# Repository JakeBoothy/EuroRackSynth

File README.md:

# Eurorack Synth
A eurorack synthesizer.

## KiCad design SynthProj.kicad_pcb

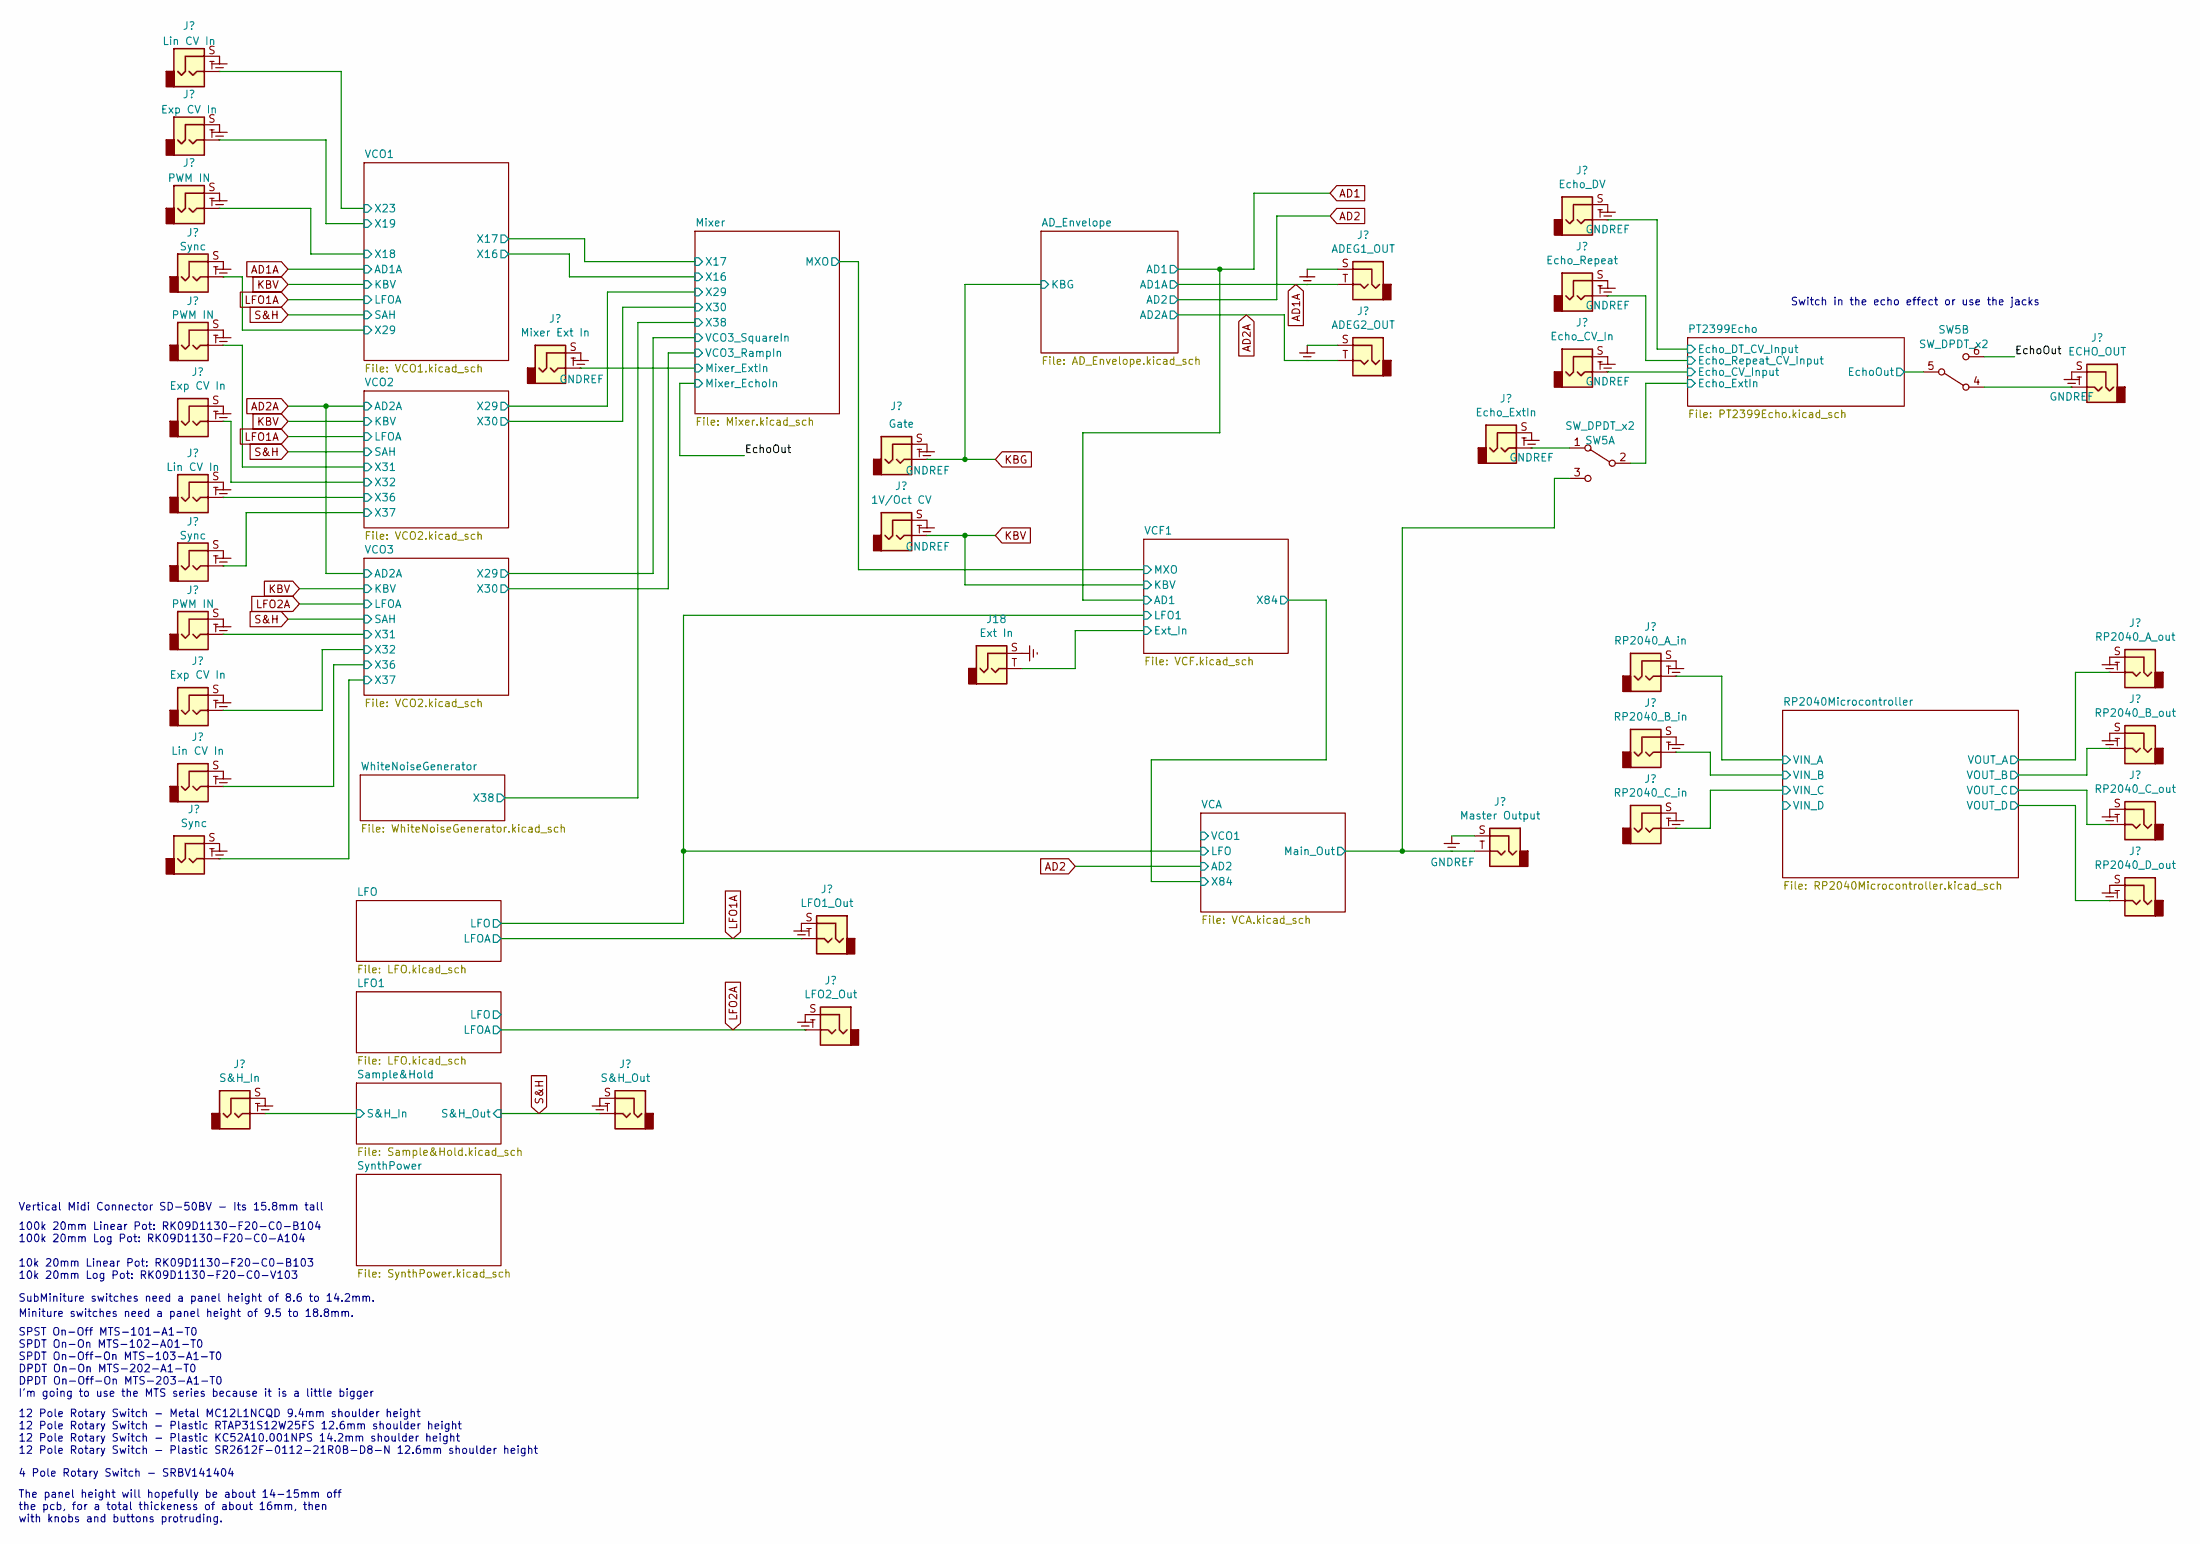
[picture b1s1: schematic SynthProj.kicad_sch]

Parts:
J1, J9, J17: PWM IN; PJ-301-BM
J2, J8, J19: Exp CV In; PJ-301-BM
J3, J7, J22: Lin CV In; PJ-301-BM
J4, J23, J24: Sync; PJ-301-BM
J6: S&H_In; PJ-301-BM
J10: Mixer Ext In; PJ-301-BM
J11: S&H_Out; PJ-301-BM
J12: LFO1_Out; PJ-301-BM
J13: Gate; PJ-301-BM
J14: 1V/Oct CV; PJ-301-BM
J16: LFO2_Out; PJ-301-BM
J18: Ext In; PJ-301-BM
J20: ADEG1_OUT; PJ-301-BM
J21: ADEG2_OUT; PJ-301-BM
J25: Master Output; PJ-301-BM
J26: RP2040_A_in; PJ-301-BM
J27: RP2040_B_in; PJ-301-BM
J28: RP2040_C_in; PJ-301-BM
J30: Echo_DV; PJ-301-BM
J31: Echo_Repeat; PJ-301-BM
J32: Echo_CV_In; PJ-301-BM
J33: Echo_ExtIn; PJ-301-BM
J34: ECHO_OUT; PJ-301-BM
J35: RP2040_A_out; PJ-301-BM
J36: RP2040_B_out; PJ-301-BM
J37: RP2040_C_out; PJ-301-BM
J38: RP2040_D_out; PJ-301-BM
SW5: SW_DPDT_x2; SMTS-202

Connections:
/EchoOut: SW5.6 (C); also elsewhere on the board
/Mixer/Mixer_ExtIn: J10.T; also elsewhere on the board
/PT2399Echo/EchoOut: SW5.5 (B); also elsewhere on the board
/PT2399Echo/Echo_CV_Input: J32.T; also elsewhere on the board
/PT2399Echo/Echo_DT_CV_Input: J30.T; also elsewhere on the board
/PT2399Echo/Echo_ExtIn: SW5.2 (B); also elsewhere on the board
/PT2399Echo/Echo_Repeat_CV_Input: J31.T; also elsewhere on the board
/RP2040Microcontroller/VIN_A: J26.T; also elsewhere on the board
/RP2040Microcontroller/VIN_B: J27.T; also elsewhere on the board
/RP2040Microcontroller/VIN_C: J28.T; also elsewhere on the board
/RP2040Microcontroller/VOUT_A: J35.T; also elsewhere on the board
/RP2040Microcontroller/VOUT_B: J36.T; also elsewhere on the board
/RP2040Microcontroller/VOUT_C: J37.T; also elsewhere on the board
/RP2040Microcontroller/VOUT_D: J38.T; also elsewhere on the board
/Sample&Hold/S&H_In: J6.T; also elsewhere on the board
/VCA/Main_Out: J25.T, SW5.3 (C); also elsewhere on the board
/VCO1/X18: J9.T; also elsewhere on the board
/VCO1/X19: J8.T; also elsewhere on the board
/VCO1/X23: J7.T; also elsewhere on the board
/VCO1/X29: J24.T; also elsewhere on the board
/VCO2/X31: J1.T; also elsewhere on the board
/VCO2/X32: J2.T; also elsewhere on the board
/VCO2/X36: J3.T; also elsewhere on the board
/VCO2/X37: J23.T; also elsewhere on the board
/VCO3/X31: J17.T; also elsewhere on the board
/VCO3/X32: J19.T; also elsewhere on the board
/VCO3/X36: J22.T; also elsewhere on the board
/VCO3/X37: J4.T; also elsewhere on the board
AD1A: J20.T; also elsewhere on the board
AD2A: J21.T; also elsewhere on the board
GNDREF: J1.S, J2.S, J3.S, J4.S, J6.S, J7.S, J8.S, J9.S, J10.S, J11.S, J12.S, J13.S, J14.S, J16.S, J17.S, J18.S, J19.S, J20.S, J21.S, J22.S, J23.S, J24.S, J25.S, J26.S, J27.S, J28.S, J30.S, J31.S, J32.S, J33.S, J34.S, J35.S, J36.S, J37.S, J38.S; also elsewhere on the board
KBG: J13.T; also elsewhere on the board
KBV: J14.T; also elsewhere on the board
LFO1A: J12.T; also elsewhere on the board
LFO2A: J16.T; also elsewhere on the board
unnamed: J33.T, SW5.1 (A)
unnamed: J34.T, SW5.4 (A)
S&H: J11.T; also elsewhere on the board
X7: J18.T; also elsewhere on the board

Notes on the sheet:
SubMiniture switches need a panel height of 8.6 to 14.2mm.
Vertical Midi Connector SD-50BV - Its 15.8mm tall
Switch in the echo effect or use the jacks
100k 20mm Linear Pot: RK09D1130-F20-C0-B104 100k 20mm Log Pot: RK09D1130-F20-C0-A104 10k 20mm Linear Pot: RK09D1130-F20-C0-B103 10k 20mm Log Pot: RK09D1130-F20-C0-V103
4 Pole Rotary Switch - SRBV141404
The panel height will hopefully be about 14-15mm off the pcb, for a total thickeness of about 16mm, then with knobs and buttons protruding.
SPST On-Off MTS-101-A1-T0 SPDT On-On MTS-102-A01-T0 SPDT On-Off-On MTS-103-A1-T0 DPDT On-On MTS-202-A1-T0 DPDT On-Off-On MTS-203-A1-T0 I'm going to use the MTS series because it is a little bigger
Miniture switches need a panel height of 9.5 to 18.8mm.
12 Pole Rotary Switch - Metal MC12L1NCQD 9.4mm shoulder height 12 Pole Rotary Switch - Plastic RTAP31S12W25FS 12.6mm shoulder height 12 Pole Rotary Switch - Plastic KC52A10.001NPS 14.2mm shoulder height 12 Pole Rotary Switch - Plastic SR2612F-0112-21R0B-D8-N 12.6mm shoulder height

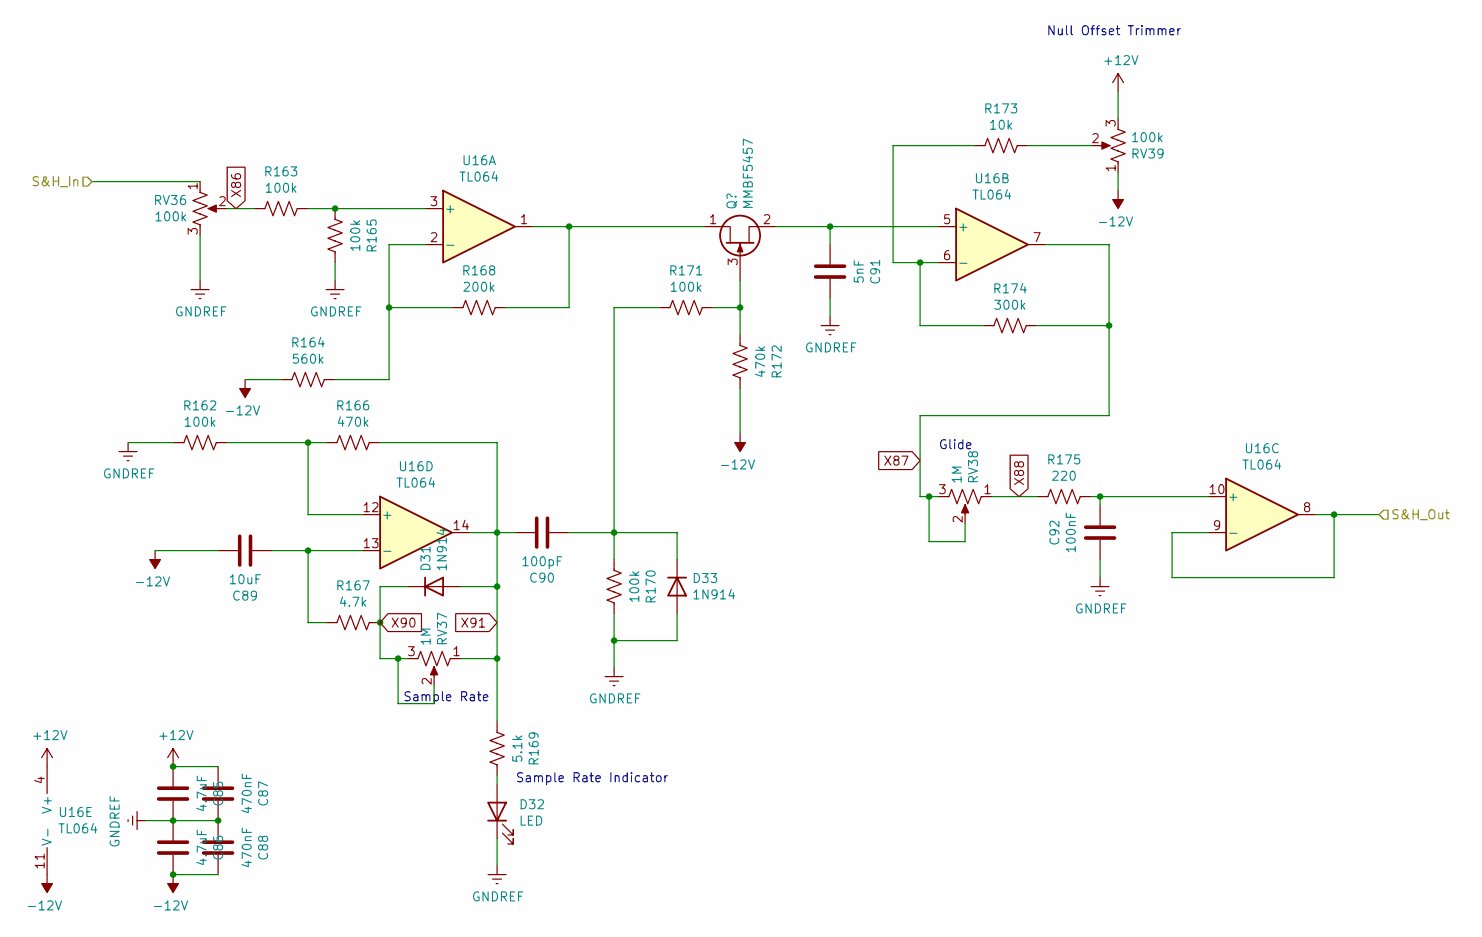
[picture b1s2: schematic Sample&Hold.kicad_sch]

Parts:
C85, C86: 4.7uF; C_0805_2012Metric
C87, C88: 470nF; C_0805_2012Metric
C89: 10uF; C_0805_2012Metric
C90: 100pF; C_0603_1608Metric
C91: 5nF; C_0603_1608Metric
C92: 100nF; C_0603_1608Metric
D31, D33: 1N914; D_SOD-323F
D32: LED; LED_0805_2012Metric
Q19: MMBF5457; SOT-23-3
R162, R163, R165, R170, R171: 100k; R_0603_1608Metric
R164: 560k; R_0603_1608Metric
R166, R172: 470k; R_0603_1608Metric
R167: 4.7k; R_0603_1608Metric
R168: 200k; R_0603_1608Metric
R169: 5.1k; R_0603_1608Metric
R173: 10k; R_0603_1608Metric
R174: 300k; R_0603_1608Metric
R175: 220; R_0603_1608Metric
RV36: 100k; Potentiometer_Alps_RK09K_Single_Vertical
RV37, RV38: 1M; Potentiometer_Alps_RK09K_Single_Vertical
RV39: 100k; Potentiometer_Bourns_TC33X_Vertical
U16: TL064; SO-14_3.9x8.65mm_P1.27mm

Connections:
+12V: C85.2, C87.2, RV39.3, U16.4 (V+); also elsewhere on the board
-12V: C86.1, C88.1, C89.1, R164.2, R172.1, RV39.1, U16.11 (V-); also elsewhere on the board
/Sample&Hold/S&H_In: RV36.1; also elsewhere on the board
GNDREF: C85.1, C86.2, C87.1, C88.2, C91.1, C92.2, D32.1 (K), D33.2 (A), R162.2, R165.1, R170.1, RV36.3; also elsewhere on the board
unnamed: D32.2 (A), R169.1
unnamed: C90.2, D33.1 (K), R170.2, R171.2
unnamed: Q19.1 (D), R168.1, U16.1
unnamed: Q19.3 (G), R171.1, R172.2
unnamed: C91.2, Q19.2 (S), U16.5 (+)
unnamed: R173.1, RV39.2
unnamed: R163.1, R165.2, U16.3 (+)
unnamed: R164.1, R168.2, U16.2 (-)
unnamed: R173.2, R174.2, U16.6 (-)
unnamed: C92.1, R175.1, U16.10 (+)
unnamed: R162.1, R166.2, U16.12 (+)
unnamed: C89.2, R167.2, U16.13 (-)
S&H: U16.8, U16.9 (-); also elsewhere on the board
X86: R163.2, RV36.2
X87: R174.1, RV38.2, RV38.3, U16.7
X88: R175.2, RV38.1
X90: D31.1 (K), R167.1, RV37.2, RV37.3
X91: C90.1, D31.2 (A), R166.1, R169.2, RV37.1, U16.14

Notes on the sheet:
Sample Rate Indicator
Sample Rate
Glide
Null Offset Trimmer

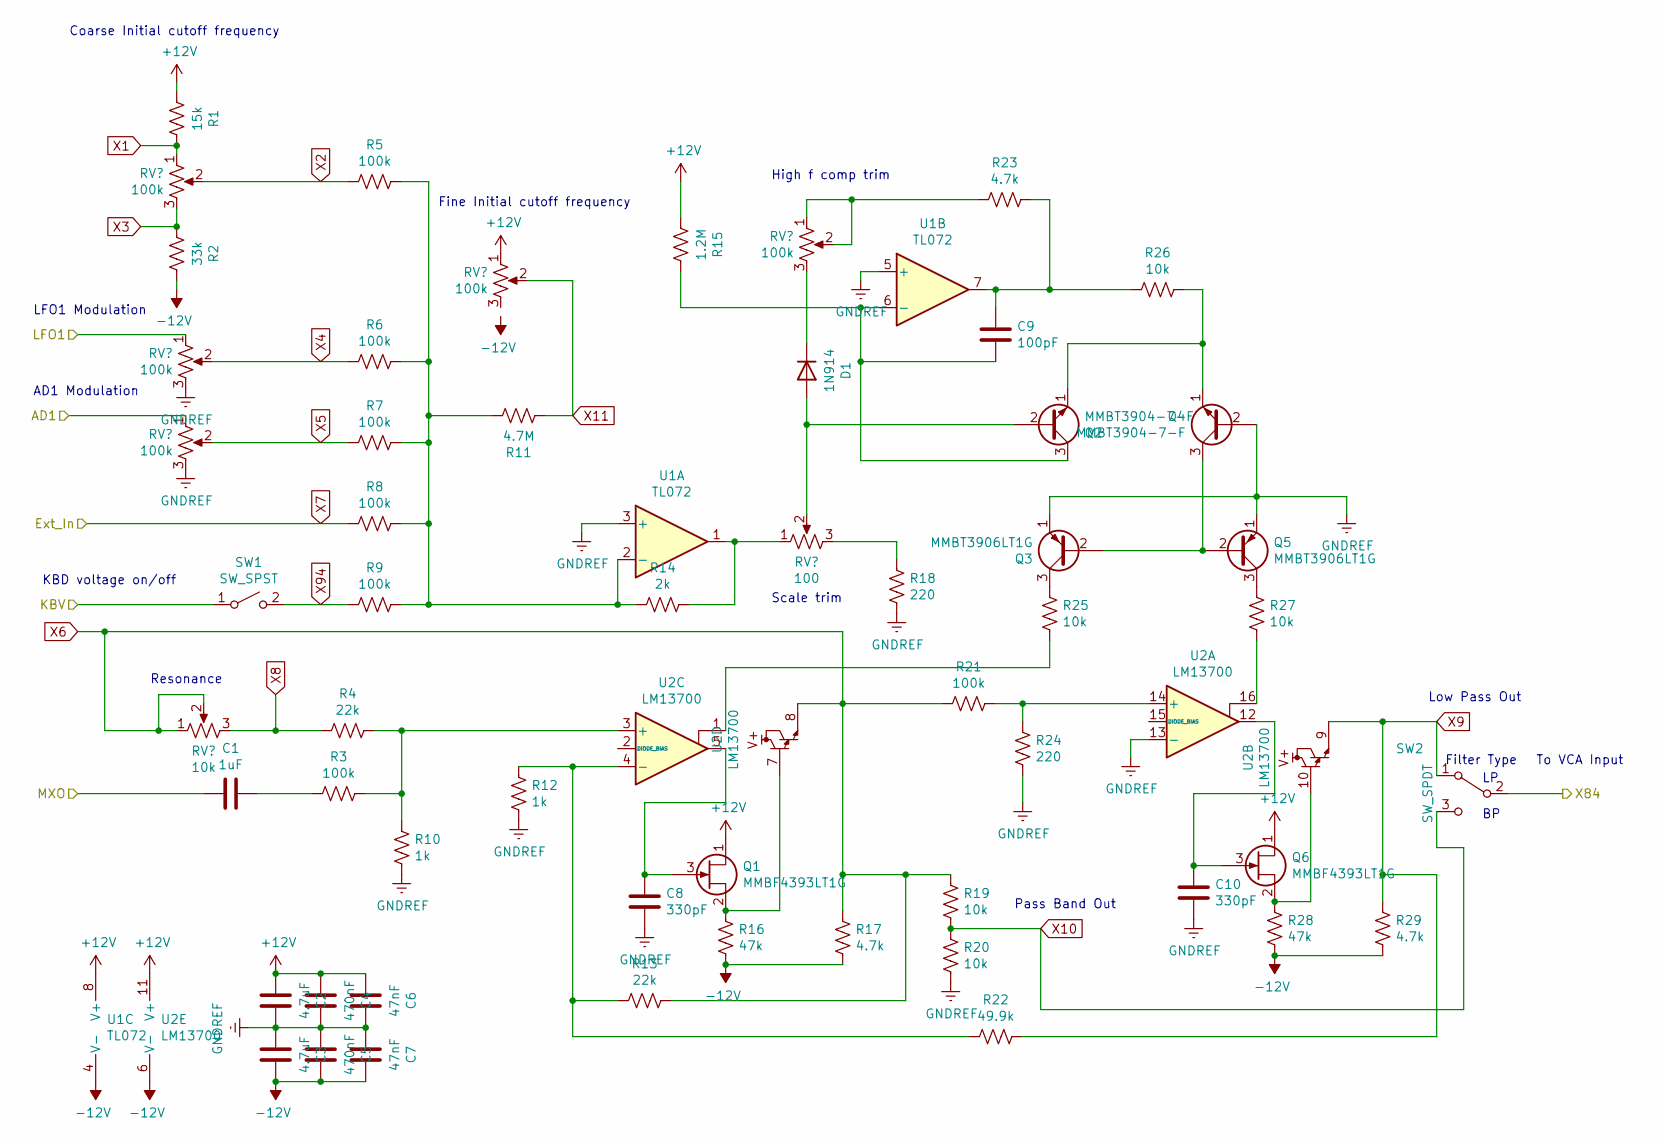
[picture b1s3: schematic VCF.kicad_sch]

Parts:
C1: 1uF; C_0805_2012Metric
C2, C3: 4.7uF; C_0805_2012Metric
C4, C5: 470nF; C_0805_2012Metric
C6, C7: 47nF; C_0603_1608Metric
C8, C10: 330pF; C_0603_1608Metric
C9: 100pF; C_0603_1608Metric
D1: 1N914; D_SOD-323F
Q1, Q6: MMBF4393LT1G; SOT-23-3
Q2, Q4: MMBT3904-7-F; SOT-23-3
Q3, Q5: MMBT3906LT1G; SOT-23-3
R1: 15k; R_0603_1608Metric
R2: 33k; R_0603_1608Metric
R3, R5, R6, R7, R8, R9, R21: 100k; R_0603_1608Metric
R4, R13: 22k; R_0603_1608Metric
R10, R12: 1k; R_0603_1608Metric
R11: 4.7M; R_0603_1608Metric
R14: 2k; R_0603_1608Metric
R15: 1.2M; R_0603_1608Metric
R16, R28: 47k; R_0603_1608Metric
R17, R23, R29: 4.7k; R_0603_1608Metric
R18, R24: 220; R_0603_1608Metric
R19, R20, R25, R26, R27: 10k; R_0603_1608Metric
R22: 49.9k; R_0603_1608Metric
RV1, RV2, RV3, RV5: 100k; Potentiometer_Alps_RK09K_Single_Vertical
RV4: 10k; Potentiometer_Alps_RK09K_Single_Vertical
RV6: 100k; Potentiometer_Bourns_TC33X_Vertical
RV7: 100; Potentiometer_Bourns_TC33X_Vertical
SW1: SW_SPST; SMTS-102
SW2: SW_SPDT; SMTS-102
U1: TL072; SOP-8_3.9x4.9mm_P1.27mm
U2: LM13700; SO-16_5.3x10.2mm_P1.27mm

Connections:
+12V: C2.2, C4.2, C6.2, Q1.1 (D), Q6.1 (D), R1.2, R15.2, RV5.1, U1.8 (V+), U2.11 (V+); also elsewhere on the board
-12V: C3.1, C5.1, C7.1, R2.1, R16.1, R17.1, R28.1, R29.1, U1.4 (V-), U2.6 (V-); also elsewhere on the board
/LFO/LFO: RV2.1; also elsewhere on the board
/Mixer/MXO: C1.2; also elsewhere on the board
/VCA/X84: SW2.2 (B); also elsewhere on the board
AD1: RV3.1; also elsewhere on the board
GNDREF: C2.1, C3.2, C4.1, C5.2, C6.1, C7.2, C8.2, C10.2, Q3.1 (E), Q4.2 (B), Q5.1 (E), R10.2, R12.2, R18.2, R20.2, R24.1, RV2.3, RV3.3, U1.3 (+), U1.5 (+), U2.13 (-); also elsewhere on the board
KBV: SW1.1 (A); also elsewhere on the board
unnamed: C1.1, R3.2
unnamed: C9.1, R23.1, R26.2, U1.7
unnamed: D1.2 (A), Q2.2 (B), RV7.2
unnamed: D1.1 (K), RV6.3
unnamed: C8.1, Q1.3 (G), U2.5
unnamed: Q1.2 (S), R16.2, U2.7
unnamed: C9.2, Q2.3 (C), R15.1, U1.6 (-)
unnamed: Q2.1 (E), Q4.1 (E), R26.1
unnamed: Q3.2 (B), Q4.3 (C), Q5.2 (B)
unnamed: Q3.3 (C), R25.1
unnamed: Q5.3 (C), R27.1
unnamed: C10.1, Q6.3 (G), U2.12
unnamed: Q6.2 (S), R28.2, U2.10
unnamed: R14.1, RV7.1, U1.1
unnamed: R18.1, RV7.3
unnamed: R23.2, RV6.1, RV6.2
unnamed: R25.2, U2.1
unnamed: R27.2, U2.16
unnamed: R5.1, R6.1, R7.1, R8.1, R9.1, R11.1, R14.2, U1.2 (-)
unnamed: R21.1, R24.2, U2.14 (+)
unnamed: R3.1, R4.1, R10.1, U2.3 (+)
unnamed: R12.1, R13.1, R22.1, U2.4 (-)
X1: R1.1, RV1.1
X2: R5.2, RV1.2
X3: R2.2, RV1.3
X4: R6.2, RV2.2
X5: R7.2, RV3.2
X6: R13.2, R17.2, R19.1, R21.2, RV4.1, RV4.2, U2.8
X7: R8.2; also elsewhere on the board
X8: R4.2, RV4.3
X9: R22.2, R29.2, SW2.1 (A), U2.9
X10: R19.2, R20.1, SW2.3 (C)
X11: R11.2, RV5.2
X94: R9.2, SW1.2 (B)

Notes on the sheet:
KBD voltage on/off
AD1 Modulation
Resonance
Low Pass Out
Fine Initial cutoff frequency
LFO1 Modulation
Coarse Initial cutoff frequency
Scale trim
To VCA Input
Filter Type
High f comp trim
Pass Band Out

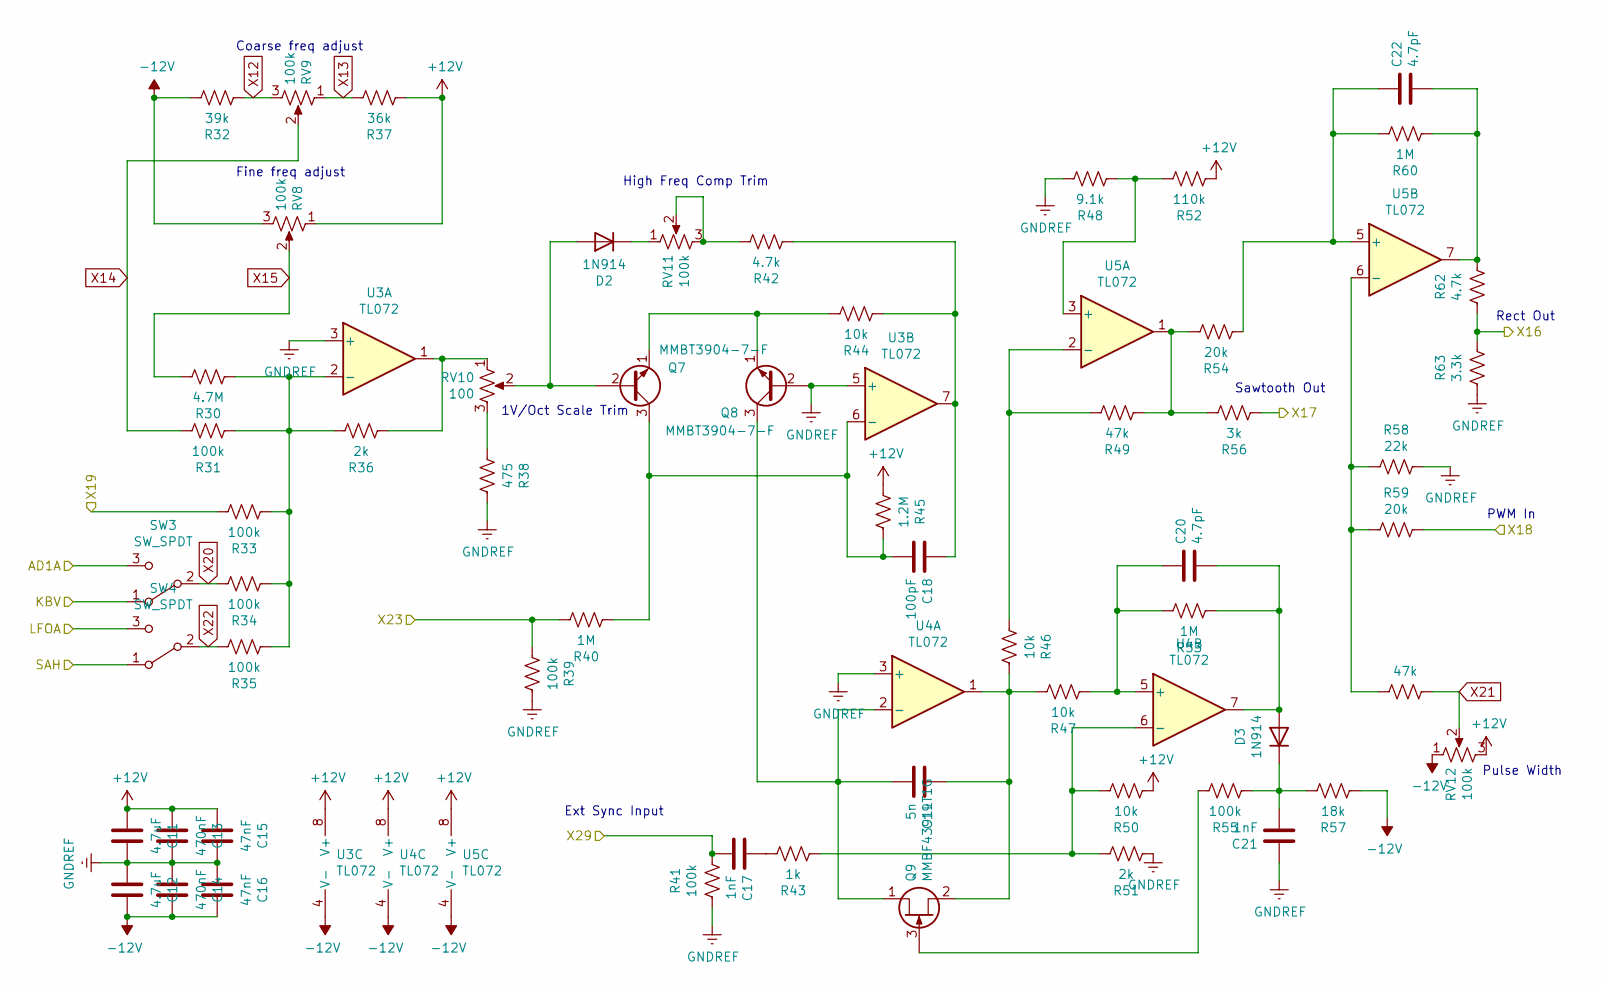
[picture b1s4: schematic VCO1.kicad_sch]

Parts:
C11, C12: 4.7uF; C_0805_2012Metric
C13, C14: 470nF; C_0805_2012Metric
C15, C16: 47nF; C_0603_1608Metric
C17, C21: 1nF; C_0603_1608Metric
C18: 100pF; C_0603_1608Metric
C19: 5n; C_0603_1608Metric
C20, C22: 4.7pF; C_0603_1608Metric
D2, D3: 1N914; D_SOD-323F
Q7, Q8: MMBT3904-7-F; SOT-23-3
Q9: MMBF4391LT1G; SOT-23-3
R30: 4.7M; R_0603_1608Metric
R31, R33, R34, R35, R39, R41, R55: 100k; R_0603_1608Metric
R32: 39k; R_0603_1608Metric
R36, R51: 2k; R_0603_1608Metric
R37: 36k; R_0603_1608Metric
R38: 475; R_0603_1608Metric
R40, R53, R60: 1M; R_0603_1608Metric
R42, R62: 4.7k; R_0603_1608Metric
R43: 1k; R_0603_1608Metric
R44, R46, R47, R50: 10k; R_0603_1608Metric
R45: 1.2M; R_0603_1608Metric
R48: 9.1k; R_0603_1608Metric
R49, R61: 47k; R_0603_1608Metric
R52: 110k; R_0603_1608Metric
R54, R59: 20k; R_0603_1608Metric
R56: 3k; R_0603_1608Metric
R57: 18k; R_0603_1608Metric
R58: 22k; R_0603_1608Metric
R63: 3.3k; R_0603_1608Metric
RV8, RV9, RV12: 100k; Potentiometer_Alps_RK09K_Single_Vertical
RV10: 100; Potentiometer_Bourns_TC33X_Vertical
RV11: 100k; Potentiometer_Bourns_TC33X_Vertical
SW3, SW4: SW_SPDT; SMTS-102
U3, U4, U5: TL072; SO-8_3.9x4.9mm_P1.27mm

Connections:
+12V: C11.2, C13.2, C15.2, R37.2, R45.2, R50.2, R52.2, RV8.1, RV12.3, U3.8 (V+), U4.8 (V+), U5.8 (V+); also elsewhere on the board
-12V: C12.1, C14.1, C16.1, R32.1, R57.2, RV8.3, RV12.1, U3.4 (V-), U4.4 (V-), U5.4 (V-); also elsewhere on the board
/Mixer/X16: R62.2, R63.1; also elsewhere on the board
/Mixer/X17: R56.2; also elsewhere on the board
/VCO1/X18: R59.1; also elsewhere on the board
/VCO1/X19: R33.1; also elsewhere on the board
/VCO1/X23: R39.2, R40.1; also elsewhere on the board
/VCO1/X29: C17.2, R41.1; also elsewhere on the board
AD1A: SW3.3 (C); also elsewhere on the board
GNDREF: C11.1, C12.2, C13.1, C14.2, C15.1, C16.2, C21.1, Q8.2 (B), R38.1, R39.1, R41.2, R48.1, R51.2, R58.1, R63.2, U3.3 (+), U3.5 (+), U4.3 (+); also elsewhere on the board
KBV: SW3.1 (A); also elsewhere on the board
LFO1A: SW4.3 (C); also elsewhere on the board
unnamed: C17.1, R43.1
unnamed: C18.1, R42.2, R44.2, U3.7
unnamed: C22.2, R60.2, R62.1, U5.7
unnamed: D2.2 (A), Q7.2 (B), RV10.2
unnamed: C20.2, D3.2 (A), R53.2, U4.7
unnamed: C21.2, D3.1 (K), R55.2, R57.1
unnamed: C18.2, Q7.3 (C), R40.2, R45.1, U3.6 (-)
unnamed: Q7.1 (E), Q8.1 (E), R44.1
unnamed: C19.2, Q8.3 (C), Q9.1 (D), U4.2 (-)
unnamed: Q9.3 (G), R55.1
unnamed: C19.1, Q9.2 (S), R46.1, R47.1, U4.1
unnamed: R36.2, RV10.1, U3.1
unnamed: R38.2, RV10.3
unnamed: R49.2, R54.1, R56.1, U5.1
unnamed: R30.2, R31.2, R33.2, R34.2, R35.2, R36.1, U3.2 (-)
unnamed: C20.1, R47.2, R53.1, U4.5 (+)
unnamed: R43.2, R50.1, R51.1, U4.6 (-)
unnamed: R48.2, R52.1, U5.3 (+)
unnamed: R46.2, R49.1, U5.2 (-)
unnamed: C22.1, R54.2, R60.1, U5.5 (+)
unnamed: R58.2, R59.2, R61.2, U5.6 (-)
S&H: SW4.1 (A); also elsewhere on the board
X12: R32.2, RV9.3
X13: R37.1, RV9.1
X14: R31.1, RV9.2
X15: R30.1, RV8.2
X20: R34.1, SW3.2 (B)
X21: R61.1, RV12.2
X22: R35.1, SW4.2 (B)

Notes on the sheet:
Pulse Width
Coarse freq adjust
High Freq Comp Trim
Fine freq adjust
Rect Out
1V/Oct Scale Trim
Ext Sync Input
PWM In
Sawtooth Out

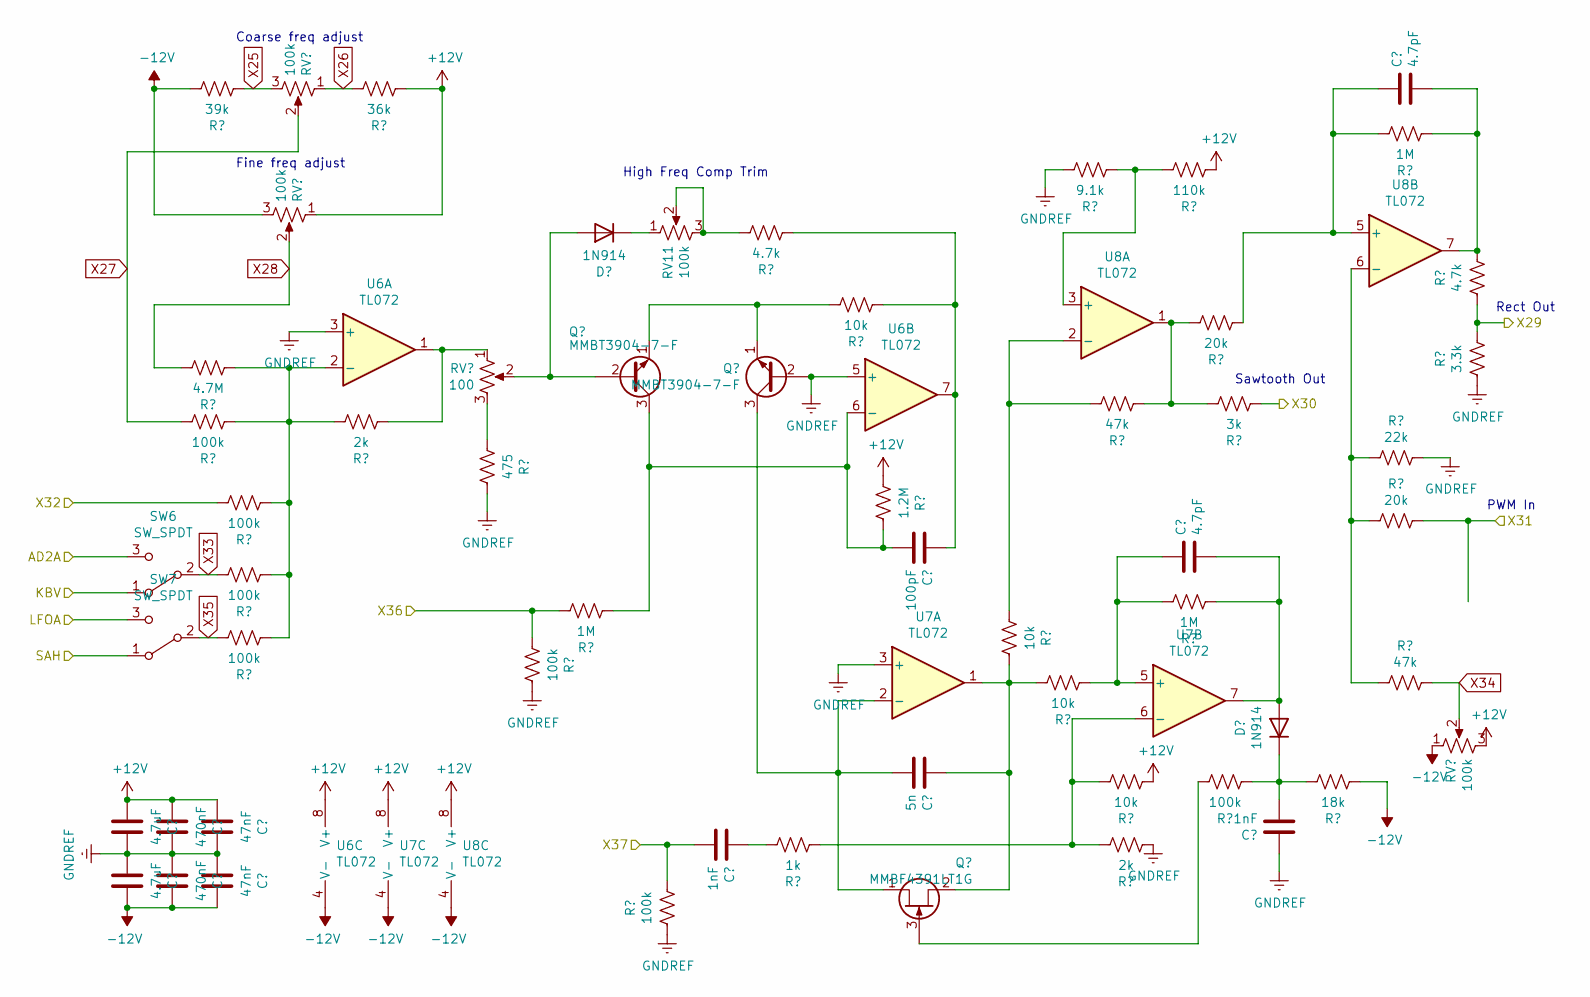
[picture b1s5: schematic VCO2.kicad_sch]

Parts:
C23, C24: 4.7uF; C_0805_2012Metric
C25, C26: 470nF; C_0805_2012Metric
C27, C28: 47nF; C_0603_1608Metric
C29, C33: 1nF; C_0603_1608Metric
C30: 100pF; C_0603_1608Metric
C31: 5n; C_0603_1608Metric
C32, C34: 4.7pF; C_0603_1608Metric
D4, D5: 1N914; D_SOD-323F
Q10, Q11: MMBT3904-7-F; SOT-23-3
Q12: MMBF4391LT1G; SOT-23-3
R64: 4.7M; R_0603_1608Metric
R65, R67, R68, R69, R73, R75, R89: 100k; R_0603_1608Metric
R66: 39k; R_0603_1608Metric
R70, R85: 2k; R_0603_1608Metric
R71: 36k; R_0603_1608Metric
R72: 475; R_0603_1608Metric
R74, R87, R94: 1M; R_0603_1608Metric
R76, R96: 4.7k; R_0603_1608Metric
R77: 1k; R_0603_1608Metric
R78, R80, R81, R84: 10k; R_0603_1608Metric
R79: 1.2M; R_0603_1608Metric
R82: 9.1k; R_0603_1608Metric
R83, R95: 47k; R_0603_1608Metric
R86: 110k; R_0603_1608Metric
R88, R93: 20k; R_0603_1608Metric
R90: 3k; R_0603_1608Metric
R91: 18k; R_0603_1608Metric
R92: 22k; R_0603_1608Metric
R97: 3.3k; R_0603_1608Metric
RV11: 100k; Potentiometer_Bourns_TC33X_Vertical
RV13, RV14, RV17: 100k; Potentiometer_Alps_RK09K_Single_Vertical
RV15: 100; Potentiometer_Bourns_TC33X_Vertical
SW6, SW7: SW_SPDT; SMTS-102
U6, U7, U8: TL072; SO-8_3.9x4.9mm_P1.27mm

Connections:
+12V: C23.2, C25.2, C27.2, R71.2, R79.2, R84.2, R86.2, RV13.1, RV17.3, U6.8 (V+), U7.8 (V+), U8.8 (V+); also elsewhere on the board
-12V: C24.1, C26.1, C28.1, R66.1, R91.2, RV13.3, RV17.1, U6.4 (V-), U7.4 (V-), U8.4 (V-); also elsewhere on the board
/Mixer/X29: R96.2, R97.1; also elsewhere on the board
/Mixer/X30: R90.2; also elsewhere on the board
/VCO2/X31: R93.1; also elsewhere on the board
/VCO2/X32: R67.1; also elsewhere on the board
/VCO2/X36: R73.2, R74.1; also elsewhere on the board
/VCO2/X37: C29.2, R75.1; also elsewhere on the board
AD2A: SW6.3 (C); also elsewhere on the board
GNDREF: C23.1, C24.2, C25.1, C26.2, C27.1, C28.2, C33.1, Q11.2 (B), R72.1, R73.1, R75.2, R82.1, R85.2, R92.1, R97.2, U6.3 (+), U6.5 (+), U7.3 (+); also elsewhere on the board
KBV: SW6.1 (A); also elsewhere on the board
LFO1A: SW7.3 (C); also elsewhere on the board
unnamed: C29.1, R77.1
unnamed: C30.1, R76.2, R78.2, U6.7
unnamed: C34.2, R94.2, R96.1, U8.7
unnamed: D4.2 (A), Q10.2 (B), RV15.2
unnamed: C32.2, D5.2 (A), R87.2, U7.7
unnamed: C33.2, D5.1 (K), R89.2, R91.1
unnamed: C30.2, Q10.3 (C), R74.2, R79.1, U6.6 (-)
unnamed: Q10.1 (E), Q11.1 (E), R78.1
unnamed: C31.2, Q11.3 (C), Q12.1 (D), U7.2 (-)
unnamed: Q12.3 (G), R89.1
unnamed: C31.1, Q12.2 (S), R80.1, R81.1, U7.1
unnamed: R70.2, RV15.1, U6.1
unnamed: R72.2, RV15.3
unnamed: R83.2, R88.1, R90.1, U8.1
unnamed: R64.2, R65.2, R67.2, R68.2, R69.2, R70.1, U6.2 (-)
unnamed: C32.1, R81.2, R87.1, U7.5 (+)
unnamed: R77.2, R84.1, R85.1, U7.6 (-)
unnamed: R82.2, R86.1, U8.3 (+)
unnamed: R80.2, R83.1, U8.2 (-)
unnamed: C34.1, R88.2, R94.1, U8.5 (+)
unnamed: R92.2, R93.2, R95.2, U8.6 (-)
S&H: SW7.1 (A); also elsewhere on the board
X25: R66.2, RV14.3; also elsewhere on the board
X26: R71.1, RV14.1; also elsewhere on the board
X27: R65.1, RV14.2; also elsewhere on the board
X28: R64.1, RV13.2; also elsewhere on the board
X33: R68.1, SW6.2 (B); also elsewhere on the board
X34: R95.1, RV17.2; also elsewhere on the board
X35: R69.1, SW7.2 (B); also elsewhere on the board

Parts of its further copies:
C94, C95: 4.7uF; C_0805_2012Metric
C96, C97: 470nF; C_0805_2012Metric
C98, C99: 47nF; C_0603_1608Metric
C100, C104: 1nF; C_0603_1608Metric
C101: 100pF; C_0603_1608Metric
C102: 5n; C_0603_1608Metric
C103, C105: 4.7pF; C_0603_1608Metric
D34, D35: 1N914; D_SOD-323F
Q20, Q25: MMBT3904-7-F; SOT-23-3
Q26: MMBF4391LT1G; SOT-23-3
R177: 4.7M; R_0603_1608Metric
R178, R180, R181, R182, R186, R188, R202: 100k; R_0603_1608Metric
R179: 39k; R_0603_1608Metric
R183, R198: 2k; R_0603_1608Metric
R184: 36k; R_0603_1608Metric
R185: 475; R_0603_1608Metric
R187, R200, R207: 1M; R_0603_1608Metric
R189, R209: 4.7k; R_0603_1608Metric
R190: 1k; R_0603_1608Metric
R191, R193, R194, R197: 10k; R_0603_1608Metric
R192: 1.2M; R_0603_1608Metric
R195: 9.1k; R_0603_1608Metric
R196, R208: 47k; R_0603_1608Metric
R199: 110k; R_0603_1608Metric
R201, R206: 20k; R_0603_1608Metric
R203: 3k; R_0603_1608Metric
R204: 18k; R_0603_1608Metric
R205: 22k; R_0603_1608Metric
R210: 3.3k; R_0603_1608Metric
RV16, RV46: 100k; Potentiometer_Bourns_TC33X_Vertical
RV43, RV44, RV47: 100k; Potentiometer_Alps_RK09K_Single_Vertical
RV45: 100; Potentiometer_Bourns_TC33X_Vertical
SW24, SW25: SW_SPDT; SMTS-102
U17, U18, U19: TL072; SO-8_3.9x4.9mm_P1.27mm

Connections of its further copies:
+12V: C94.2, C96.2, C98.2, R184.2, R192.2, R197.2, R199.2, RV43.1, RV47.3, U17.8 (V+), U18.8 (V+), U19.8 (V+); also elsewhere on the board
-12V: C95.1, C97.1, C99.1, R179.1, R204.2, RV43.3, RV47.1, U17.4 (V-), U18.4 (V-), U19.4 (V-); also elsewhere on the board
/Mixer/VCO3_RampIn: R203.2; also elsewhere on the board
/Mixer/VCO3_SquareIn: R209.2, R210.1; also elsewhere on the board
/VCO3/X31: R206.1; also elsewhere on the board
/VCO3/X32: R180.1; also elsewhere on the board
/VCO3/X36: R186.2, R187.1; also elsewhere on the board
/VCO3/X37: C100.2, R188.1; also elsewhere on the board
AD2A: SW24.3 (C); also elsewhere on the board
GNDREF: C94.1, C95.2, C96.1, C97.2, C98.1, C99.2, C104.1, Q25.2 (B), R185.1, R186.1, R188.2, R195.1, R198.2, R205.1, R210.2, U17.3 (+), U17.5 (+), U18.3 (+); also elsewhere on the board
KBV: SW24.1 (A); also elsewhere on the board
LFO2A: SW25.3 (C); also elsewhere on the board
unnamed: C100.1, R190.1
unnamed: C101.1, R189.2, R191.2, U17.7
unnamed: C105.2, R207.2, R209.1, U19.7
unnamed: D34.2 (A), Q20.2 (B), RV45.2
unnamed: D34.1 (K), RV46.1
unnamed: C103.2, D35.2 (A), R200.2, U18.7
unnamed: C104.2, D35.1 (K), R202.2, R204.1
unnamed: C101.2, Q20.3 (C), R187.2, R192.1, U17.6 (-)
unnamed: Q20.1 (E), Q25.1 (E), R191.1
unnamed: C102.2, Q25.3 (C), Q26.1 (D), U18.2 (-)
unnamed: Q26.3 (G), R202.1
unnamed: C102.1, Q26.2 (S), R193.1, R194.1, U18.1
unnamed: R183.2, RV45.1, U17.1
unnamed: R185.2, RV45.3
unnamed: R189.1, RV46.2, RV46.3
unnamed: R196.2, R201.1, R203.1, U19.1
unnamed: R177.2, R178.2, R180.2, R181.2, R182.2, R183.1, U17.2 (-)
unnamed: C103.1, R194.2, R200.1, U18.5 (+)
unnamed: R190.2, R197.1, R198.1, U18.6 (-)
unnamed: R195.2, R199.1, U19.3 (+)
unnamed: R193.2, R196.1, U19.2 (-)
unnamed: C105.1, R201.2, R207.1, U19.5 (+)
unnamed: R205.2, R206.2, R208.2, U19.6 (-)
S&H: SW25.1 (A); also elsewhere on the board
X25: R179.2, RV44.3; also elsewhere on the board
X26: R184.1, RV44.1; also elsewhere on the board
X27: R178.1, RV44.2; also elsewhere on the board
X28: R177.1, RV43.2; also elsewhere on the board
X33: R181.1, SW24.2 (B); also elsewhere on the board
X34: R208.1, RV47.2; also elsewhere on the board
X35: R182.1, SW25.2 (B); also elsewhere on the board

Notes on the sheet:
PWM In
Fine freq adjust
High Freq Comp Trim
Coarse freq adjust
Sawtooth Out
Rect Out

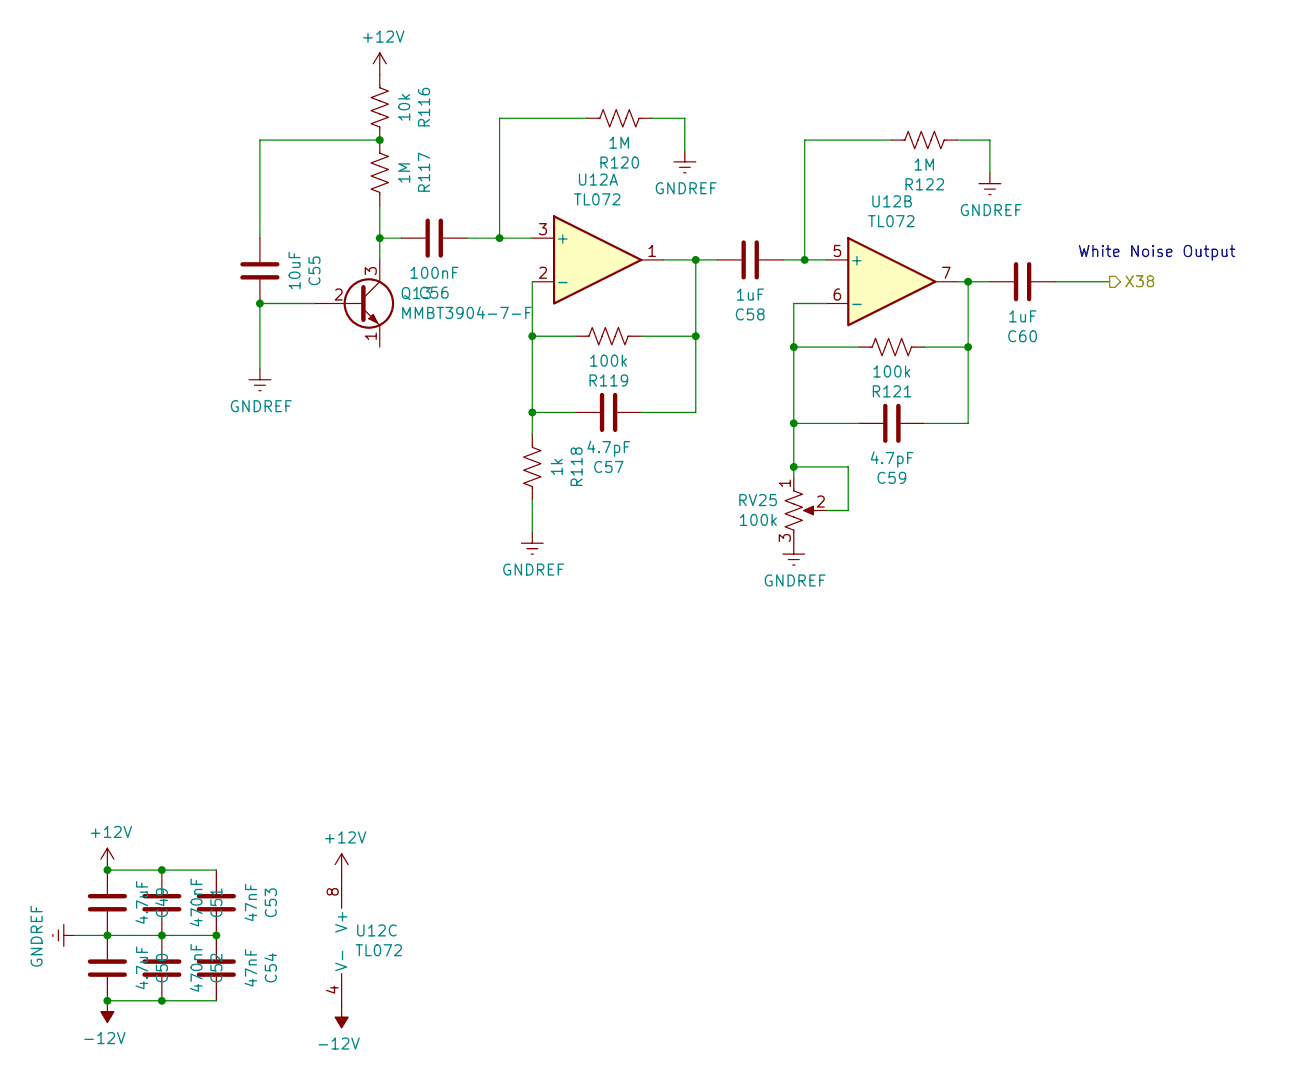
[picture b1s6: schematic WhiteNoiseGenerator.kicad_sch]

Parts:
C49, C50: 4.7uF; C_0805_2012Metric
C51, C52: 470nF; C_0805_2012Metric
C53, C54: 47nF; C_0603_1608Metric
C55: 10uF; C_0805_2012Metric
C56: 100nF; C_0603_1608Metric
C57, C59: 4.7pF; C_0603_1608Metric
C58, C60: 1uF; C_0805_2012Metric
Q13: MMBT3904-7-F; SOT-23-3
R116: 10k; R_0603_1608Metric
R117, R120, R122: 1M; R_0603_1608Metric
R118: 1k; R_0603_1608Metric
R119, R121: 100k; R_0603_1608Metric
RV25: 100k; Potentiometer_Bourns_TC33X_Vertical
U12: TL072; SOP-8_3.9x4.9mm_P1.27mm

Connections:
+12V: C49.2, C51.2, C53.2, R116.2, U12.8 (V+); also elsewhere on the board
-12V: C50.1, C52.1, C54.1, U12.4 (V-); also elsewhere on the board
/Mixer/X38: C60.2; also elsewhere on the board
GNDREF: C49.1, C50.2, C51.1, C52.2, C53.1, C54.2, C55.1, Q13.2 (B), R118.1, R120.2, R122.2, RV25.3; also elsewhere on the board
unnamed: C55.2, R116.1, R117.2
unnamed: C57.2, C58.1, R119.2, U12.1
unnamed: C59.2, C60.1, R121.2, U12.7
unnamed: C56.1, Q13.3 (C), R117.1
unnamed: C56.2, R120.1, U12.3 (+)
unnamed: C57.1, R118.2, R119.1, U12.2 (-)
unnamed: C58.2, R122.1, U12.5 (+)
unnamed: C59.1, R121.1, RV25.1, RV25.2, U12.6 (-)

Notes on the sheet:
White Noise Output
